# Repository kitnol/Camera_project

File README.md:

| Supported Targets | ESP32-S3 |
| ----------------- | -------- |

# Basic Console Example (`esp_console_repl`)

(See the README.md file in the upper level 'examples' directory for more information about examples.)

This example illustrates the usage of the REPL (Read-Eval-Print Loop) APIs of the [Console Component](https://docs.espressif.com/projects/esp-idf/en/latest/esp32/api-reference/system/console.html#console) to create an interactive shell on the ESP chip. The interactive shell running on the ESP chip can then be controlled/interacted with over a serial interface. This example supports UART and USB interfaces.

The interactive shell implemented in this example contains a wide variety of commands, and can act as a basis for applications that require a command-line interface (CLI).

Compared to the [advanced console example](../advanced), this example requires less code to initialize and run the console. `esp_console_repl` API handles most of the details. If you'd like to customize the way console works (for example, process console commands in an existing task), please check the advanced console example.

## How to use example

This example can be used on boards with UART and USB interfaces. The sections below explain how to set up the board and configure the example.

### Using with UART

When UART interface is used, this example should run on any commonly available Espressif development board. UART interface is enabled by default (`CONFIG_ESP_CONSOLE_UART_DEFAULT` option in menuconfig). No extra configuration is required.

### Using with USB_SERIAL_JTAG

*NOTE: We recommend to disable the secondary console output on chips with USB_SERIAL_JTAG since the secondary serial is output-only and would not be very useful when using a console application. This is why the secondary console output is deactivated per default (CONFIG_ESP_CONSOLE_SECONDARY_NONE=y)*

On chips with USB_SERIAL_JTAG peripheral, console example can be used over the USB serial port.

* First, connect the USB cable to the USB_SERIAL_JTAG interface.
* Second, run `idf.py menuconfig` and enable `CONFIG_ESP_CONSOLE_USB_SERIAL_JTAG` option.

For more details about connecting and configuring USB_SERIAL_JTAG (including pin numbers), see the IDF Programming Guide:
* [ESP32-C3 USB_SERIAL_JTAG](https://docs.espressif.com/projects/esp-idf/en/stable/esp32c3/api-guides/usb-serial-jtag-console.html)
* [ESP32-S3 USB_SERIAL_JTAG](https://docs.espressif.com/projects/esp-idf/en/stable/esp32s3/api-guides/usb-serial-jtag-console.html)

### Using with USB CDC (USB_OTG peripheral)

USB_OTG peripheral can also provide a USB serial port which works with this example.

* First, connect the USB cable to the USB_OTG peripheral interface.
* Second, run `idf.py menuconfig` and enable `CONFIG_ESP_CONSOLE_USB_CDC` option.

For more details about connecting and configuring USB_OTG (including pin numbers), see the IDF Programming Guide:
* [ESP32-S2 USB_OTG](https://docs.espressif.com/projects/esp-idf/en/stable/esp32s2/api-guides/usb-otg-console.html)
* [ESP32-S3 USB_OTG](https://docs.espressif.com/projects/esp-idf/en/stable/esp32s3/api-guides/usb-otg-console.html)

### Other configuration options

This example has an option to store the command history in Flash. This option is enabled by default.

To disable this, run `idf.py menuconfig` and disable `CONFIG_CONSOLE_STORE_HISTORY` option.

### Build and Flash

Build the project and flash it to the board, then run monitor tool to view serial output:

```
idf.py -p PORT flash monitor
```

(Replace PORT with the name of the serial port to use.)

(To exit the serial monitor, type ``Ctrl-]``.)

See the Getting Started Guide for full steps to configure and use ESP-IDF to build projects.

## Example Output

Enter the `help` command get a full list of all available commands. The following is a sample session of the Console Example where a variety of commands provided by the Console Example are used.

On ESP32, GPIO15 may be connected to GND to remove the boot log output.

```
This is an example of ESP-IDF console component.
Type 'help' to get the list of commands.
Use UP/DOWN arrows to navigate through command history.
Press TAB when typing command name to auto-complete.
[esp32]> help
help
  Print the list of registered commands

free
  Get the total size of heap memory available

restart
  Restart the program

deep_sleep  [-t <t>] [--io=<n>] [--io_level=<0|1>]
  Enter deep sleep mode. Two wakeup modes are supported: timer and GPIO. If no
  wakeup option is specified, will sleep indefinitely.
  -t, --time=<t>  Wake up time, ms
      --io=<n>  If specified, wakeup using GPIO with given number
  --io_level=<0|1>  GPIO level to trigger wakeup

join  [--timeout=<t>] <ssid> [<pass>]
  Join WiFi AP as a station
  --timeout=<t>  Connection timeout, ms
        <ssid>  SSID of AP
        <pass>  PSK of AP

[esp32]> free
257200
[esp32]> deep_sleep -t 1000
I (146929) deep_sleep: Enabling timer wakeup, timeout=1000000us
I (619) heap_init: Initializing. RAM available for dynamic allocation:
I (620) heap_init: At 3FFAE2A0 len 00001D60 (7 KiB): DRAM
I (626) heap_init: At 3FFB7EA0 len 00028160 (160 KiB): DRAM
I (645) heap_init: At 3FFE0440 len 00003BC0 (14 KiB): D/IRAM
I (664) heap_init: At 3FFE4350 len 0001BCB0 (111 KiB): D/IRAM
I (684) heap_init: At 40093EA8 len 0000C158 (48 KiB): IRAM

This is an example of ESP-IDF console component.
Type 'help' to get the list of commands.
Use UP/DOWN arrows to navigate through command history.
Press TAB when typing command name to auto-complete.
[esp32]> join --timeout 10000 test_ap test_password
I (182639) connect: Connecting to 'test_ap'
I (184619) connect: Connected
[esp32]> free
212328
[esp32]> restart
I (205639) restart: Restarting
I (616) heap_init: Initializing. RAM available for dynamic allocation:
I (617) heap_init: At 3FFAE2A0 len 00001D60 (7 KiB): DRAM
I (623) heap_init: At 3FFB7EA0 len 00028160 (160 KiB): DRAM
I (642) heap_init: At 3FFE0440 len 00003BC0 (14 KiB): D/IRAM
I (661) heap_init: At 3FFE4350 len 0001BCB0 (111 KiB): D/IRAM
I (681) heap_init: At 40093EA8 len 0000C158 (48 KiB): IRAM

This is an example of ESP-IDF console component.
Type 'help' to get the list of commands.
Use UP/DOWN arrows to navigate through command history.
Press TAB when typing command name to auto-complete.
[esp32]>

```

## Troubleshooting

### Line Endings

The line endings in the Console Example are configured to match particular serial monitors. Therefore, if the following log output appears, consider using a different serial monitor (e.g. Putty for Windows) or modify the example's [UART configuration](#Configuring-UART-and-VFS).

```
This is an example of ESP-IDF console component.
Type 'help' to get the list of commands.
Use UP/DOWN arrows to navigate through command history.
Press TAB when typing command name to auto-complete.
Your terminal application does not support escape sequences.
Line editing and history features are disabled.
On Windows, try using Putty instead.
esp32>
```

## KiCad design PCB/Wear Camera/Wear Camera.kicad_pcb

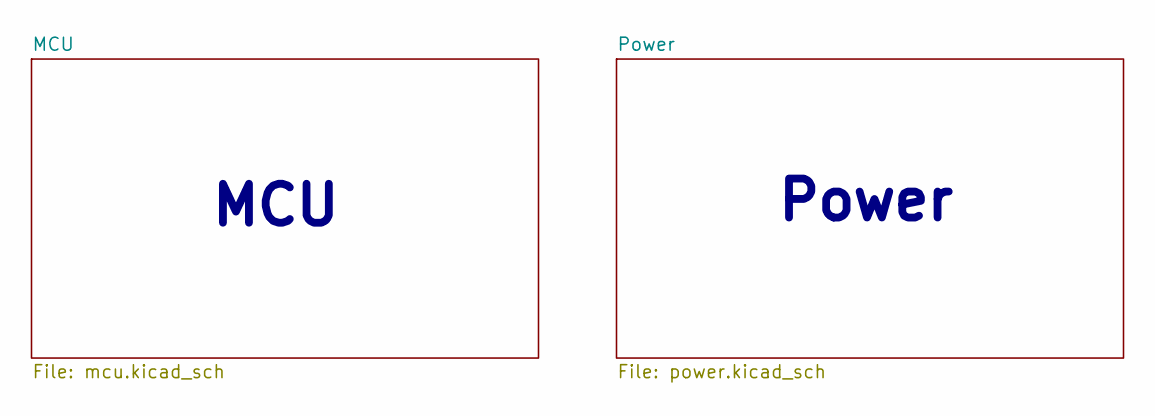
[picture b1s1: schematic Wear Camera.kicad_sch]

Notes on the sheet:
Power
MCU

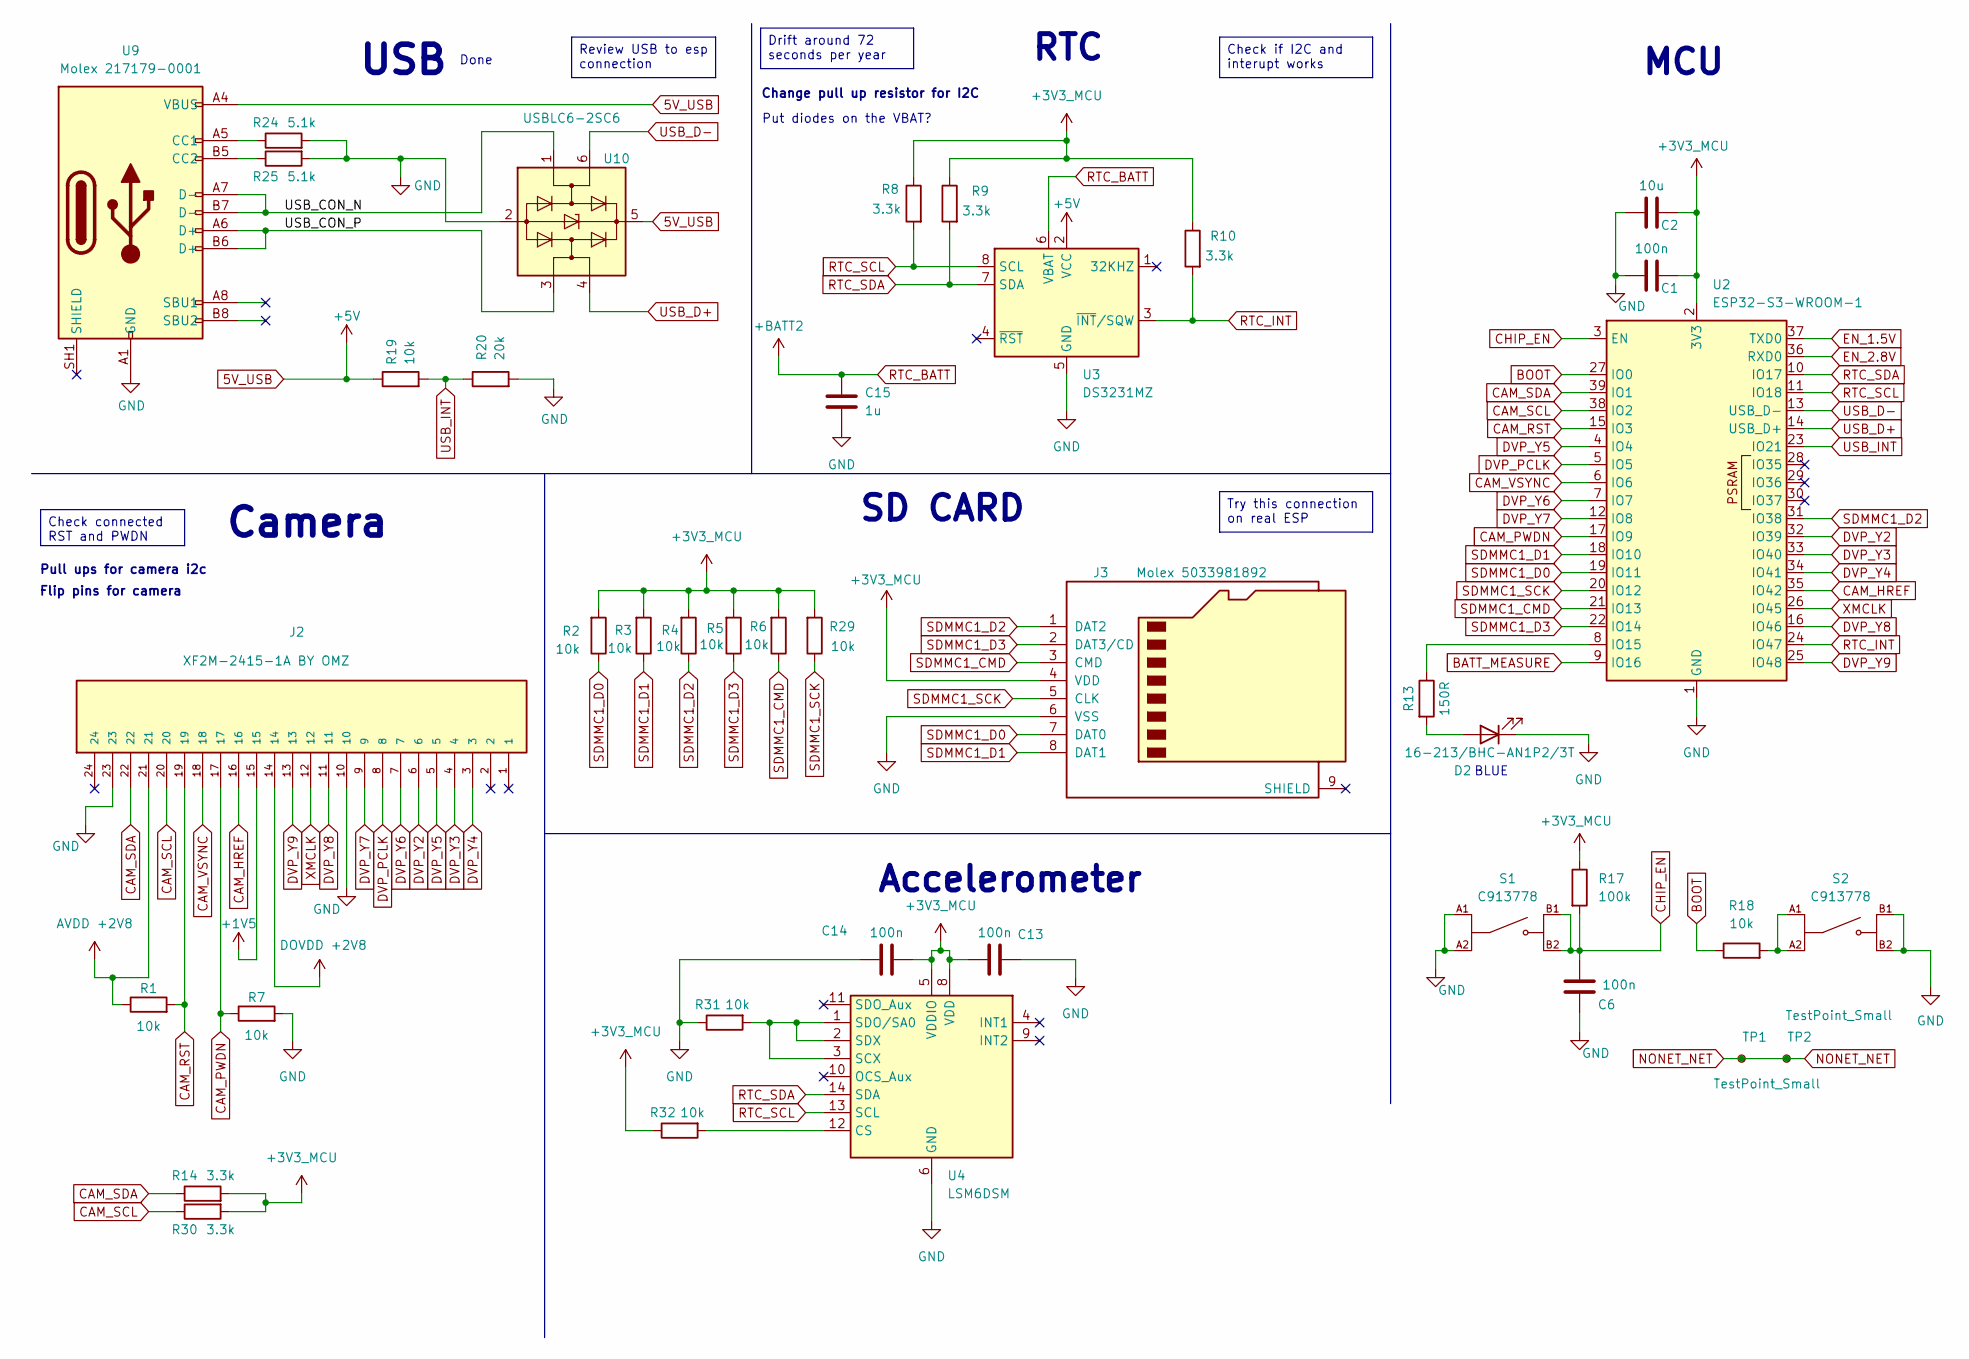
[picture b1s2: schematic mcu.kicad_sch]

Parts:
C1, C6, C13, C14: 100n; C_0402_1005Metric
C2: 10u; C_0402_1005Metric
C15: 1u; C_0402_1005Metric
D2: 16-213/BHC-AN1P2/3T; D_0402_1005Metric
J2: XF2M-2415-1A BY OMZ; OMRON_XF2M-2415-1A; PARTREV L
J3: Molex 5033981892; CONN_503398-1892_MOL
R1, R2, R3, R4, R5, R6, R7, R18, R19, R29, R31, R32: 10k; R_0402_1005Metric
R8, R9, R10, R14, R30: 3.3k; R_0402_1005Metric
R13: 150R; R_0402_1005Metric
R17: 100k; R_0402_1005Metric
R20: 20k; R_0402_1005Metric
R24, R25: 5.1k; R_0805_2012Metric_Pad1.20x1.40mm_HandSolder
S1, S2: C913778; SW_EVPBB4A9B000; DIGI-KEY_PART_NUMBER P19888CT-ND
TP1, TP2: TestPoint_Small; TestPoint_Pad_1.0x1.0mm
U2: ESP32-S3-WROOM-1
U3: DS3231MZ; SOIC-8_3.9x4.9mm_P1.27mm
U4: LSM6DSM; LGA-14_3x2.5mm_P0.5mm_LayoutBorder3x4y
U9: Molex 217179-0001; MOLEX_2171790001
U10: USBLC6-2SC6; SOT-23-6

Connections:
5V_USB: R19.1, U3.2 (VCC), U9.A4 (VBUS), U9.A9 (VBUS), U10.5 (VBUS); also elsewhere on the board
+1V5: J2.15; also elsewhere on the board
+2V8: J2.14, J2.21, R1.1; also elsewhere on the board
+3V3_MCU: C1.2, C2.2, C13.1, C14.2, J3.4 (VDD), R2.2, R3.2, R4.2, R5.2, R6.2, R8.1, R9.1, R10.1, R14.2, R17.1, R29.2, R30.2, R32.1, U2.2 (3V3), U4.5 (VDDIO), U4.8 (VDD); also elsewhere on the board
/MCU/USB_CON_N: U9.A7 (D-), U9.B7 (D-), U10.1 (I/O1)
/MCU/USB_CON_P: U9.A6 (D+), U9.B6 (D+), U10.3 (I/O2)
BATT_MEASURE: U2.9 (IO16); also elsewhere on the board
BOOT: R18.1, U2.27 (IO0)
CAM_HREF: J2.16, U2.35 (IO42)
CAM_PWDN: J2.17, R7.1, U2.17 (IO9)
CAM_RST: J2.19, R1.2, U2.15 (IO3)
CAM_SCL: J2.20, R30.1, U2.38 (IO2)
CAM_SDA: J2.22, R14.1, U2.39 (IO1)
CAM_VSYNC: J2.18, U2.6 (IO6)
CHIP_EN: C6.2, R17.2, S1.B1, S1.B2, U2.3 (EN)
DVP_PCLK: J2.8, U2.5 (IO5)
DVP_Y2: J2.6, U2.32 (IO39)
DVP_Y3: J2.4, U2.33 (IO40)
DVP_Y4: J2.3, U2.34 (IO41)
DVP_Y5: J2.5, U2.4 (IO4)
DVP_Y6: J2.7, U2.7 (IO7)
DVP_Y7: J2.9, U2.12 (IO8)
DVP_Y8: J2.11, U2.16 (IO46)
DVP_Y9: J2.13, U2.25 (IO48)
EN_1.5V: U2.37 (TXD0); also elsewhere on the board
EN_2.8V: U2.36 (RXD0); also elsewhere on the board
GND: C1.1, C2.1, C6.1, C13.2, C14.1, C15.2, D2.1 (K), J2.10, J2.23, J3.6 (VSS), R7.2, R20.2, R24.2, R25.2, R31.1, S1.A1, S1.A2, S2.B1, S2.B2, U2.1 (GND), U2.40 (GND), U2.41 (GND), U3.5 (GND), U4.6 (GND), U4.7 (GND), U9.A1 (GND), U9.A12 (GND), U10.2 (GND); also elsewhere on the board
NONET_NET: TP1.1, TP2.1
unnamed: D2.2 (A), R13.2
unnamed: R18.2, S2.A1, S2.A2
unnamed: R13.1, U2.8 (IO15)
unnamed: R32.2, U4.12 (CS)
unnamed: R31.2, U4.1 (SDO/SA0), U4.2 (SDX), U4.3 (SCX)
unnamed: R24.1, U9.A5 (CC1)
unnamed: R25.1, U9.B5 (CC2)
RTC_BATT: C15.1, U3.6 (VBAT); also elsewhere on the board
RTC_INT: R10.2, U2.24 (IO47), U3.3 (~INT/SQW)
RTC_SCL: R8.2, U2.11 (IO18), U3.8 (SCL), U4.13 (SCL)
RTC_SDA: R9.2, U2.10 (IO17), U3.7 (SDA), U4.14 (SDA)
SDMMC1_CMD: J3.3 (CMD), R6.1, U2.21 (IO13)
SDMMC1_D0: J3.7 (DAT0), R2.1, U2.19 (IO11)
SDMMC1_D1: J3.8 (DAT1), R3.1, U2.18 (IO10)
SDMMC1_D2: J3.1 (DAT2), R4.1, U2.31 (IO38)
SDMMC1_D3: J3.2 (DAT3/CD), R5.1, U2.22 (IO14)
SDMMC1_SCK: J3.5 (CLK), R29.1, U2.20 (IO12)
USB_D+: U2.14 (USB_D+), U10.4 (I/O2)
USB_D-: U2.13 (USB_D-), U10.6 (I/O1)
USB_INT: R19.2, R20.1, U2.23 (IO21)
XMCLK: J2.12, U2.26 (IO45)

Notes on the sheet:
BLUE
Accelerometer
Done
Change pull up resistor for I2C
Pull ups for camera i2c
SD CARD
MCU
Flip pins for camera
USB
Camera
RTC
Put diodes on the VBAT?
Drift around 72 seconds per year
Try this connection on real ESP
Check if I2C and interupt works
Check connected RST and PWDN
Review USB to esp connection

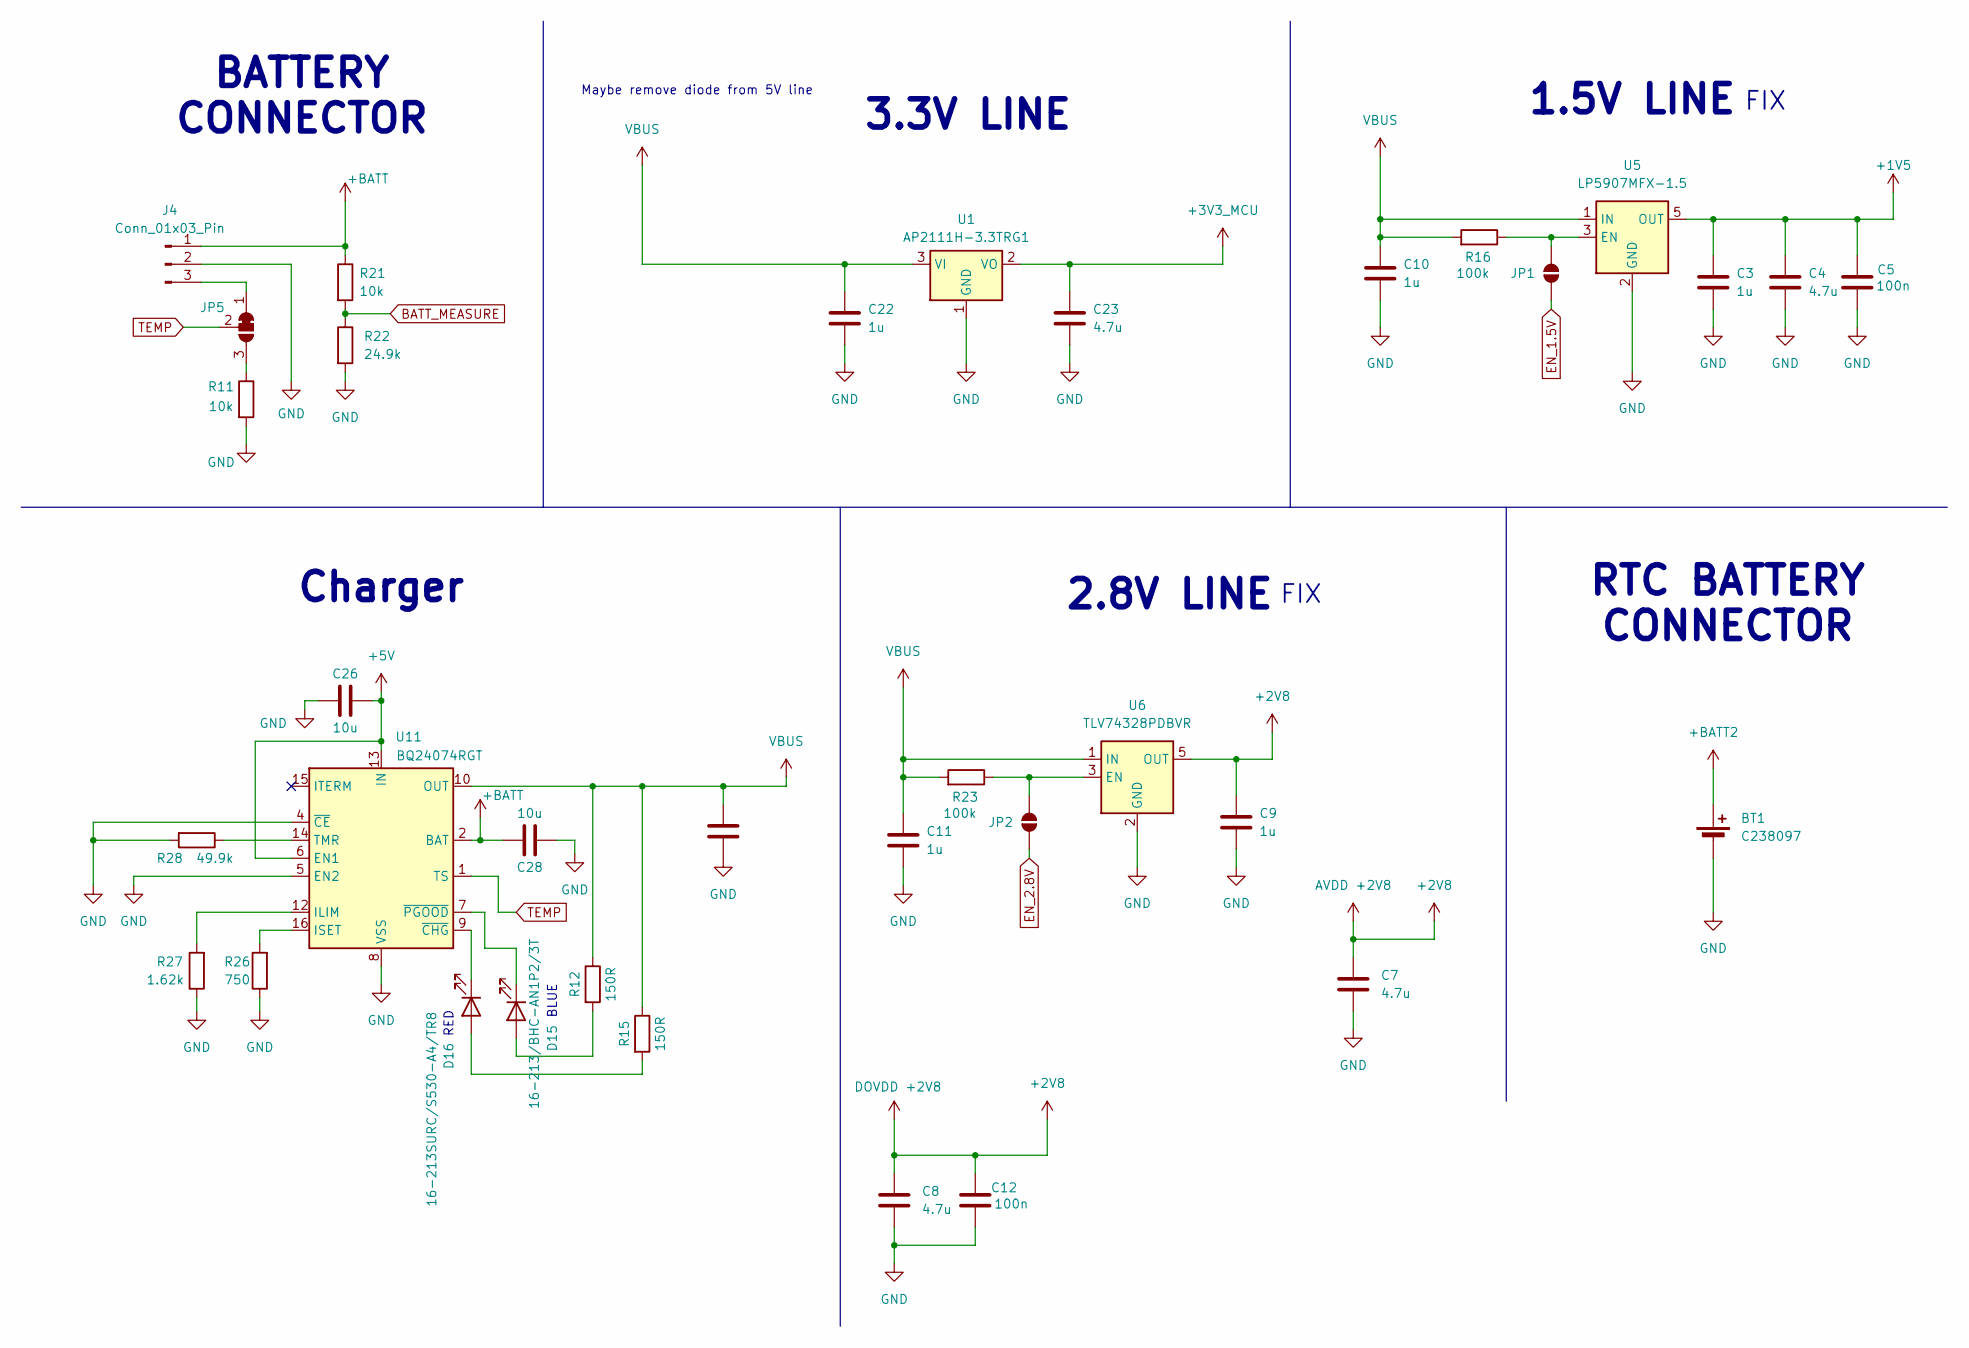
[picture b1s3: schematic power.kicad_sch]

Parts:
BT1: C238097; BAT_3000
C3, C9, C10, C11, C22: 1u; C_0402_1005Metric
C4, C7, C8, C23: 4.7u; C_0402_1005Metric
C5, C12: 100n; C_0402_1005Metric
C26, C27, C28: 10u; C_1210_3225Metric_Pad1.33x2.70mm_HandSolder
D15: 16-213/BHC-AN1P2/3T; D_0402_1005Metric
D16: 16-213SURC/S530-A4/TR8; D_0402_1005Metric
J4: Conn_01x03_Pin; JST_SH_SM03B-SRSS-TB_1x03-1MP_P1.00mm_Horizontal
JP1, JP2: SolderJumper_2_Open; SolderJumper-2_P1.3mm_Open_RoundedPad1.0x1.5mm
JP5: SolderJumper_3_Bridged12; SolderJumper-3_P1.3mm_Bridged2Bar12_RoundedPad1.0x1.5mm
R11, R21: 10k; R_0402_1005Metric
R12, R15: 150R; R_0402_1005Metric
R16, R23: 100k; R_0402_1005Metric
R22: 24.9k; R_0402_1005Metric
R26: 750; R_0402_1005Metric
R27: 1.62k; R_0402_1005Metric
R28: 49.9k; R_0402_1005Metric
U1: AP2111H-3.3TRG1; SOT-223
U5: LP5907MFX-1.5; SOT-23-5
U6: TLV74328PDBVR; SOT-23-5
U11: BQ24074RGT; VQFN-16-1EP_3x3mm_P0.5mm_EP1.6x1.6mm

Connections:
5V_USB: C26.2, U11.6 (EN1), U11.13 (IN); also elsewhere on the board
+1V5: C3.1, C4.1, C5.2, U5.5 (OUT); also elsewhere on the board
+2V8: C7.1, C8.1, C9.1, C12.2, U6.5 (OUT); also elsewhere on the board
+3V3_MCU: C23.1, U1.2 (VO); also elsewhere on the board
+BATT: C28.1, J4.1, R21.1, U11.2 (BAT), U11.3 (BAT)
BATT_MEASURE: R21.2, R22.1; also elsewhere on the board
EN_1.5V: JP1.1 (A); also elsewhere on the board
EN_2.8V: JP2.1 (A); also elsewhere on the board
GND: BT1.2 (-), C3.2, C4.2, C5.1, C7.2, C8.2, C9.2, C10.2, C11.2, C12.1, C22.2, C23.2, C26.1, C27.2, C28.2, J4.2, R11.2, R22.2, R26.1, R27.1, R28.2, U1.1 (GND), U5.2 (GND), U6.2 (GND), U11.4 (~CE), U11.5 (EN2), U11.8 (VSS), U11.17 (VSS); also elsewhere on the board
unnamed: D15.2 (A), R12.2
unnamed: D15.1 (K), U11.7 (~PGOOD)
unnamed: D16.2 (A), R15.2
unnamed: D16.1 (K), U11.9 (~CHG)
unnamed: J4.3, JP5.1 (A)
unnamed: JP1.2 (B), R16.1, U5.3 (EN)
unnamed: JP2.2 (B), R23.1, U6.3 (EN)
unnamed: JP5.3 (B), R11.1
unnamed: R27.2, U11.12 (ILIM)
unnamed: R26.2, U11.16 (ISET)
unnamed: R28.1, U11.14 (TMR)
RTC_BATT: BT1.1 (+); also elsewhere on the board
TEMP: JP5.2 (C), U11.1 (TS)
VBUS: C10.1, C11.1, C22.1, C27.1, R12.1, R15.1, R16.2, R23.2, U1.3 (VI), U5.1 (IN), U6.1 (IN), U11.10 (OUT), U11.11 (OUT)

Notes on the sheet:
RTC BATTERY CONNECTOR
FIX
2.8V LINE
Charger
Maybe remove diode from 5V line
3.3V LINE
BATTERY CONNECTOR
BLUE
1.5V LINE
RED

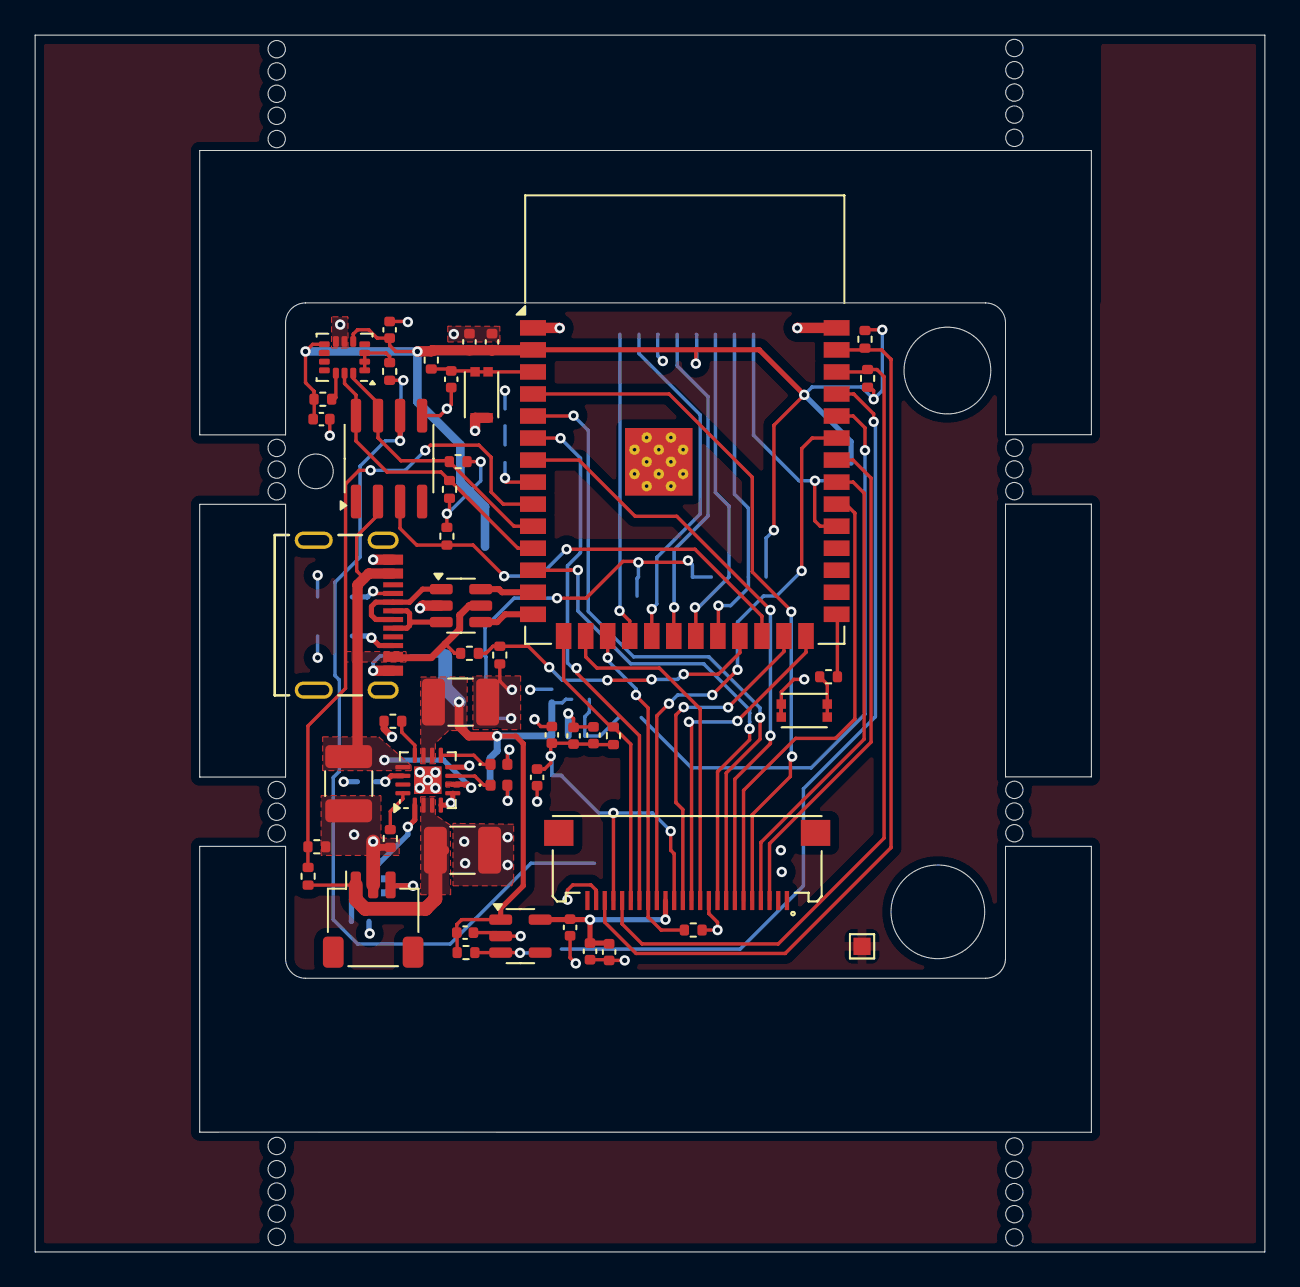
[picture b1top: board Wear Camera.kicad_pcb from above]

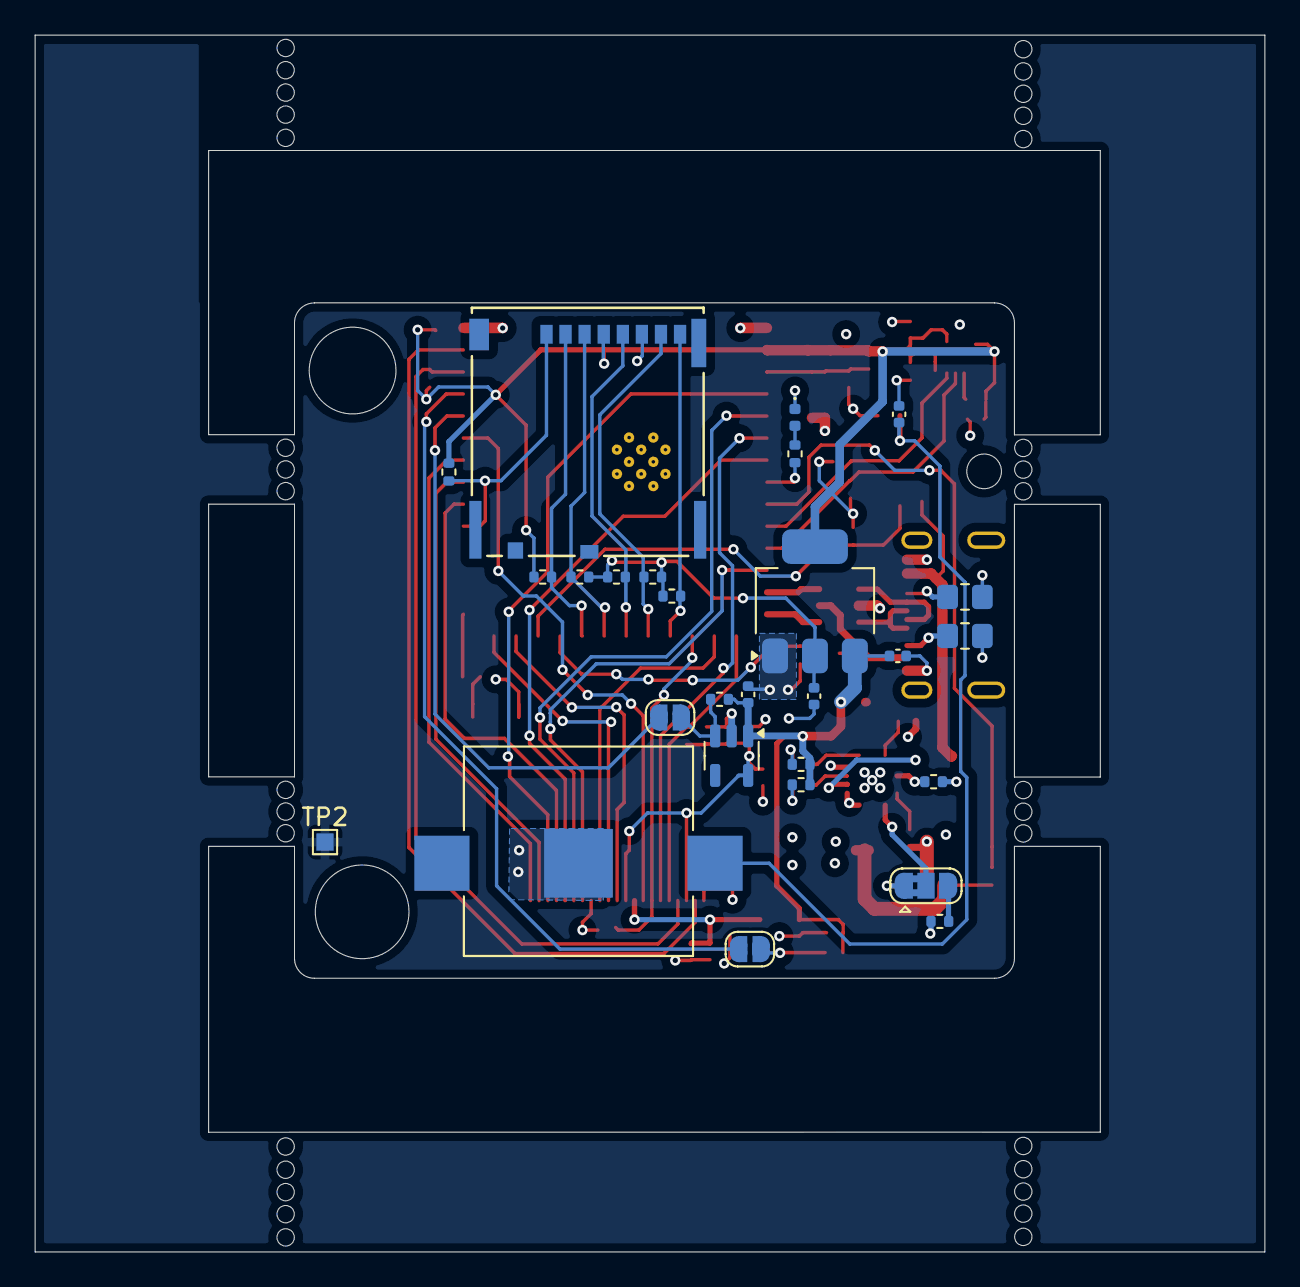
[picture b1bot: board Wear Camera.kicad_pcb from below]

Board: 4 copper layers, 70.9 x 70.1 mm, 75 parts (27 on the bottom side), 63 nets.

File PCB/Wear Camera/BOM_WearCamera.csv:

Id;Designator;Footprint;Quantity;Designation;JLC PCB
1;C27,C26,C28;C_1210_3225Metric_Pad1.33x2.70mm_HandSolder;3;10u;
2;R24,R25;R_0805_2012Metric_Pad1.20x1.40mm_HandSolder;2;5.1k;
3;U9;MOLEX_2171790001;1;Molex 217179-0001;
4;R17;R_0402_1005Metric_Pad0.72x0.64mm_HandSolder;1;100k;
5;U3;SOIC-8_3.9x4.9mm_P1.27mm;1;DS3231MZ;
6;C7,C8;C_0603_1608Metric_Pad1.08x0.95mm_HandSolder;2;4.7u;
7;R18,R11,;R_0402_1005Metric_Pad0.72x0.64mm_HandSolder;2;10k;
7;R21,R19;R_0402_1005Metric_Pad0.72x0.64mm_HandSolder;2;10k;
8;SW2,SW1;KSR231GLFS_CNK;2;SW_Push;
9;U4;TSOT-23-5;1;ADPL40502AUJZ-1.5-R7;
10;R23,R16;R_0603_1608Metric_Pad0.98x0.95mm_HandSolder;2;100k;
11;R12,R15,R13;R_0402_1005Metric_Pad0.72x0.64mm_HandSolder;3;150R;
12;C1,C5,C6,C12;C_0402_1005Metric_Pad0.74x0.62mm_HandSolder;4;100n;
13;U2;ESP32-S3-WROOM-1;1;ESP32-S3-WROOM-1;
14;R9,R8,R10;R_0603_1608Metric_Pad0.98x0.95mm_HandSolder;9;47k;
14;R4,R2,R6,R5,R3,R29;R_0603_1608Metric_Pad0.98x0.95mm_HandSolder;9;47k;
15;J1;JST_PH_S2B-PH-K_1x02_P2.00mm_Horizontal;1;Conn_01x02_Pin;
16;C2;C_0402_1005Metric_Pad0.74x0.62mm_HandSolder;1;10u;
17;J3;CONN_503398-1892_MOL;1;Molex 5033981892;
18;C10,C9,C3,C11,;C_0603_1608Metric_Pad1.08x0.95mm_HandSolder;4;1u;
18;C22;C_0603_1608Metric_Pad1.08x0.95mm_HandSolder;1;1u;
19;J2;FFC2B35-24-T;1;FFC2B35-24-T;
20;D15,;LED_0603_1608Metric_Pad1.05x0.95mm_HandSolder;1;150060GS55040;
20;D2;LED_0603_1608Metric_Pad1.05x0.95mm_HandSolder;1;150060GS55040;
21;D16;LED_0603_1608Metric_Pad1.05x0.95mm_HandSolder;1;150060RS55040;
22;TP3,TP2;TestPoint_Pad_D1.5mm;2;TestPoint_Small;
23;C23,C4;C_0402_1005Metric_Pad0.74x0.62mm_HandSolder;2;4.7u;
24;R26;R_0603_1608Metric_Pad0.98x0.95mm_HandSolder;1;750;
25;R1,R7;R_0805_2012Metric_Pad1.20x1.40mm_HandSolder;2;10k;
26;U5;TSOT-23-5;1;ADPL40502AUJZ-2.8-R7;
27;U10;SOT-23-6;1;USBLC6-2SC6;
28;U11;VQFN-16-1EP_3x3mm_P0.5mm_EP1.6x1.6mm;1;BQ24074RGT;
29;BT1;BatteryHolder_Keystone_3002_1x2032;1;Battery_Cell;
30;U1;SOT-223;1;AP2111H-3.3TRG1;
31;R22;R_0603_1608Metric_Pad0.98x0.95mm_HandSolder;1;24.9k;
32;R20;R_0402_1005Metric_Pad0.72x0.64mm_HandSolder;1;20k;
33;R28;R_0603_1608Metric_Pad0.98x0.95mm_HandSolder;1;49.9k;
34;D1,D4;D_SMA;2;D;
35;R27;R_0603_1608Metric_Pad0.98x0.95mm_HandSolder;1;1.62k;

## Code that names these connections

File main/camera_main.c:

#include <stdio.h>
#include <stdlib.h>
#include <string.h>
#include <sys/unistd.h>
#include <sys/stat.h>
#include "freertos/FreeRTOS.h"
#include "freertos/task.h"
#include "esp_heap_caps.h"

#include "esp_system.h"
#include "esp_log.h"
#include "esp_console.h"


#include "esp_camera.h"
#include "esp_vfs_dev.h"
#include "esp_vfs_fat.h"
#include "sdmmc_cmd.h"
#include "driver/sdmmc_host.h"

#include "nvs.h"
#include "nvs_flash.h"
#include "cmd_system.h"
#include "cmd_nvs.h"
#include "argtable3/argtable3.h"

#include "driver/i2c_master.h"
#include "driver/i2c.h"
#include "driver/i2c_master.h"
#include "driver/i2c_slave.h"
#include "esp_mac.h"
#include <portmacro.h>

#include "esp_sleep.h"
#include "driver/uart.h"
#include "driver/gpio.h"
#include "hal/gpio_types.h"

#include "esp_partition.h"
#include "tinyusb.h"
#include "tusb_msc_storage.h"
#include "diskio_impl.h"
#include "diskio_sdmmc.h"

#include "ds3231.h"

#include "esp_adc/adc_oneshot.h"
#include "esp_adc/adc_cali.h"
#include "esp_adc/adc_cali_scheme.h"
#include "soc/adc_channel.h"
#include "esp_timer.h"

#define CAM_PIN_PWDN 9  // Power down pin (not used)
#define CAM_PIN_RESET 3 // Reset pin (not used)
#define CAM_PIN_XCLK 45 // External clock (safe pin) +
#define CAM_PIN_SIOD 1  // I2C SDA (safe pin) +
#define CAM_PIN_SIOC 2  // I2C SCL (safe pin) +

#define CAM_PIN_D7 48   // Data 7 (safe pin) +
#define CAM_PIN_D6 46   // Data 6 (safe pin) +
#define CAM_PIN_D5 8    // Data 5 (safe pin) +
#define CAM_PIN_D4 7    // Data 4 (safe pin) +
#define CAM_PIN_D3 4    // Data 3 (safe pin) +
#define CAM_PIN_D2 41   // Data 2 (safe pin) +
#define CAM_PIN_D1 40   // Data 1 (safe pin) +
#define CAM_PIN_D0 39   // Data 0 (safe pin) +
#define CAM_PIN_VSYNC 6 // Vertical sync (safe pin) +
#define CAM_PIN_HREF 42 // Horizontal reference (safe pin)
#define CAM_PIN_PCLK 5  // Pixel clock (safe pin) +

#define CAM_PWR CAM_PIN_PWDN
#define CAM_VREG_28V 

// SD card pin configuration (SDMMC)
#define SD_PIN_SCK 12
#define SD_PIN_CMD 13
#define SD_PIN_D0 11
#define SD_PIN_D1 10
#define SD_PIN_D2 38
#define SD_PIN_D3 14

#define PIN_NUM_MISO SD_PIN_D0  // D0
#define PIN_NUM_MOSI SD_PIN_CMD // CMD
#define PIN_NUM_CLK SD_PIN_SCK  // CLK
#define PIN_NUM_CS SD_PIN_D3    // D3 (not used in 4-line mode but defined)
#define PIN_NUM_D1 SD_PIN_D1    // D1
#define PIN_NUM_D2 SD_PIN_D2    // D2

// SD card pin configuration (SPI mode)
#define PIN_NUM_MISO SD_PIN_D0
#define PIN_NUM_MOSI SD_PIN_CMD
#define PIN_NUM_CLK SD_PIN_SCK
#define PIN_NUM_CS SD_PIN_D3

#define LED_PIN 15
#define USB_INT 21
#define BAT_VOLTAGE 16

#define RTC_SDA 17
#define RTC_SCL 18

#define MOUNT_POINT "/sdcard"
sdmmc_card_t *card_handle;
static bool sd_card_mounted = false;

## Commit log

2025-09-03 Console app
2025-09-03 Main logic
2025-09-09 Fixed cam_hal.c recursion issue
2025-10-01 Login function
2025-10-01 Flash functionality
2025-10-08 DS3231 tracking
2025-10-09 All needed functionality
2025-10-22 less power consumption
2025-10-22 Fixed issue with unabling to save a picture after poweroff
2025-10-23 Clearing and oprimising for less power
2025-10-26 Decreased to 11mAh
2025-10-27 BMP files save works
2025-10-28 Optimisation of saving function
2025-10-29 Dual core start
2025-10-29 Dual core processign of sd card, 10.5mA
2025-11-11 Not good wnough
2025-11-12 Some understanding
2025-11-12 Turning on and off functionality
2025-11-16 logs printing
2025-11-16 Login works
2025-11-17 Disconnect works
2025-12-10 Exe file
2025-12-10 Update supported targets in README
2025-12-10 Cleaning
2025-12-10 brighter images
2025-12-12 GUI update - ability to update soft on cameras
2025-12-12 clean
2025-12-12 Add esptool as submodule
2025-12-14 Time seetting button
2025-12-14 Image gain manual
2025-12-15 Images fixes, PCB, 3D models
